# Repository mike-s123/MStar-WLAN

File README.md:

# MStar-WLAN

### What's new

Now supports collecting data in an [RRD](https://oss.oetiker.ch/rrdtool/), and charting that data using [JavascriptRRD](http://javascriptrrd.sourceforge.net). The interval for traditional logging can now be set. Updated hardware for USB Type-C.

## Overview

This project includes both a software and hardware design for interfacing to a [Morningstar](https://www.morningstarcorp.com/) solar controller via wireless LAN (WiFi). It's 99.99% working, with features still being added. The development core is an ESP32-WROVER-B 16MB (~$5 from Mouser) or an ESP32 DevkitC v4. A complete build should be ~$40, ignoring your time. Those platforms were chosen because they're available with a relatively large flash (16 MiB) for storing files, which allows having documentation and support for multiple solar controllers on-board. Supports MS-View compatible logging of controller info to an SD card, in addition to a debugging log. There's support for monitoring and configuration via a web interface, Modbus/TCP, and a RESTful JSON API. The UI fits well on a cell phone screen.

A core with less flash memory should work fine as long as the "data" directory will fit. The code supports moving content from flash to the SD Card. If a file is not found in flash, it will look for it on the SD Card. Delete everything in the "data" directory, copy everything from "data-small" into "data", and then copy everything in the "Put on SD Card - small" directory onto an SD Card to use an ESP32 board with less flash. The additional flash memory on the recommended modules is there in order to support all the static files even without an SD Card present. An SD Card is required for logging and charting.

It is written using the [Arduino IDE](https://www.arduino.cc/en/Main/Software), which is a bit "odd", hence code being split for clarity amongst multiple .h files. If you know how to do it better, please contribute. Yes, I know some of the code is butt-ugly. But it works. Function over form.

The printed circuit board was done in [Eagle](https://www.autodesk.com/products/eagle/overview).

Development has been done testing against the Prostar MPPT and Prostar PWM Gen3 controllers, and the information/config files for those have been provided. Other controllers will need to have register definition .csv files (see data/csv_file_desc.txt) added. Might need to do some work for register datatypes - Morningstar has many (really, what were they thinking creating one based on a 16 bit int, n·316.67·2^-15, and multiple similar) and they've changed over time. It should also be able to support Sunsavers (SSDuo, SS-MPPT), and Tristar (TS-45, TS-60, TS-MPPT-x) controllers (i.e. ones supporting Modbus). Morningstar isn't consistent with naming or numbering the registers, so such support will require more than just creating the .csv files. PS.h supports ProStar MPPT and PWM models and can be used as a template on how to support other models. Changes to _local.js_ may also be needed.

MODBUS-TCP works with Morningstar's MSView, allowing it to be used to monitor and configure a controller wirelessly. To do that, in MSView, do "Devices/Manual connection", select your controller type, select Connection Type Remote, and enter the IP address or DNS name of the MStar-WLAN. OK. Then right click on the controller in the left column and "connect." MSView first downloads any logs, so may take a minute before much else happens. It should work with any controller supporting MODBUS, it doesn't depend on the specific support for a controller, so if nothing else, it can be a wireless alternative to their USB/RS-232 to MeterBus converters (other than for doing firmware updates).

## Getting Started

The code will run on a bare ESP32 devboard, but obviously can't talk to a controller so the status and config pages won't do much. But you can check it out without much effort.

To do anything useful, hardware is needed to interface with a Morningstar controller. Morningstar uses a proprietary half-duplex (open collector, see /data/img/Schematic.png) Modbus interface. A circuit board layout is provided which includes all the necessary interfacing circuitry, even drawing power from the Morningstar controller. It supports an optional real time clock to support timestamped logging. It also supports ntp, so even without an RTC it can timestamp logs if it has a WLAN connection to the Internet.

Circuit board info is found in the "hardware/pcb" directory, where there are Eagle .brd, .sch and .lbr files, along with some parts info. The .zip file contains CAM files ready to send to [JLCPCB](https://jlcpcb.com/quote#/) to get boards made. Currently, 5 boards will cost you less than $10, if you will wait about a month to get them. The PCB was made to allow either "through hole" components (with an ESP32 DevkitC), or SMT ones (using a WROVER). If you use a DevkitC, note that 16 MiB ones aren't easy to find, so you'll probably still want to have the SD Card (which is needed for logging and charting).

I usually have a few circuit boards around. If you can contribute to the project, contact me and I might send you one. Even if you can't contribute, I might sell you one for a very reasonable price. If you don't solder, and want a pre-built one, contact me - this isn't meant to be a money maker (it's a hobby project), but I do value my time.

### Prerequisites

Development is currently being done with Arduino IDE 1.8.13, and tracking espressif / arduino-esp32ESP32 

Library requirements are noted in the .ino file. The [ESP32](https://github.com/espressif/arduino-esp32) core for Arduino needs to be installed. I follow the current development branch. View the README in the forArduinoIDE folder for info on setting up a custom board and partitions in the Arduino IDE (for Windoze, anyway).

Initially, the "data" directory needs to be uploaded to the board from the IDE (using the [arduino-esp32fs-plugin](https://github.com/me-no-dev/arduino-esp32fs-plugin)) or via OTA (Utility tab, will require files on the SD Card).

Uploadable code (MStar-WLAN.ino.esp32.bin) and flash (MStar-WLAN.littlefs.bin) binaries are provided here, which can be flashed using the OTA capability after the initial setup. 

The data/ctl/*.csv files are used to define the different controllers. data/csv_file_desc.txt describes the format.

## Operation

Using a standard "rollover" (tabs on the same side of the cable) 6P6C ("RJ12") cable, connect to the Meterbus port of a Morningstar controller. Don't worry - it's protected if wired wrong. A 4P4C cable should also work, if it's short (fewer wires for power).

The MStar-WLAN will initially come up as a wireless access point with SSID starting with "MStar" and a PSK of "morningstar". It will have an address of 192.168.4.1. 

The web interface has some minimal security. Any page which allows configuration changes is protected with default username "admin", password "setup". To do an Over-The-Air (OTA) firmware update or change security settings, the default username is "admin", password "update".

SSID, names and passwords can be changed (Utility tab, Security settings). To reset to defaults, press and hold the BOOT button for more than 5 seconds after powering up (WLAN LED will fast blink when you're held the button long enough).

Connecting to http://192.168.4.1/ will display the main status page. Other pages are shown along the top. "Utility/Wireless settings" will allow you to connect to a wireless network, from which the MStar-WLAN will get an address via DHCP (check your DHCP server to see what address it received). You can then connect to the internal web server at that address. The firmware also informs the DCHP server with a (statistically) unique hostname of the form "MStar-WLAN-xxxxxx", where the xs are the last 3 octets of the MAC address in hex.

OTA updates are done from the Utility tab, "Update WLAN module firmware" link. OTA updates of the flash (/data) image are also possible. File names are "MStar-WLAN.ino.esp32.bin" and "MStar-WLAN.littlefs.bin". 

## Known issues

When powered by the controller, it will sometimes reset at 2AM. I think this is somehow related to the ezTime library, which is really the only thing that time is special to (it's the DST changeover time for my timezone). It doesn't seem to happen when powered by USB, and doesn't seem to happen with a PS-MPPT (only a PWM). Perhaps a short race condition which causes a greater than normal power draw. It's not a big issue - the solar controller isn't affected, and we'll simply reboot and resume operation in about a minute.

## Support

There is none, although you can certainly ask - if you're having a problem, you've probably found something which I'll eventually run into. You'll get a better response if you can well document a bug. This was a personal project, I'm freely offering it to others for non-commercial use. Feel free to contribute back if you can (don't do github pull requests, that would just be another thing for me to figure out how to make work, I'm not a regular git user.). Things which need attention or might be an important future direction are commented with "TODO".

## General answers to any question (pick one)

Yes.

No.

That's an important future direction.

That's a significant third-party opportunity.

## More Info

More info may be found under the data directory.

## Current work

The hardware supports one of the cheap Chinese DS3231 Real Time Clock boards. The software can be configured to connect to an NTP server, and if it does it will keep the RTC in sync (and trim its oscillator more accurately, too!). Either a good network connection is needed (for NTP), or an RTC, for accurate logging. 

## Important future directions

Possible additions: Include support for additional controllers (if someone has a broken one which might still talk MODBUS, feel free to donate). <s>Allow changing user/pass for config and update.</s> Static IP config. SMTP - email notifications for error or out-of-range conditions (or even daily updates). <s>Logging/graphing.</s> Support for simultaneous connection to multiple controllers. <s>Async web server.</s> Chunked responses. Provide "one click" charging settings for different batteries. Backup/restore settings. <s>Support connection to multiple, alternate SSIDs</s> (done). MQTT. SNMP. Serial passthrough, to allow a direct MS-View connection and firmware upgrades via USB. <s>Move large files to SD card.</s> ???.
 
## Author

* **Mike Sauve** - [mike-s123](https://github.com/mike-s123/)
Programming is not my day job, so don't be harsh about style or efficiency. Function over form. It's working for me, I hope it works for you. I formally learned on FORTRAN and PL/C. Later BASIC, assembly, and bash with a small bit of python. 98% as a hobby. OO stuff is foreign to me. 

## License and copyrights

First up - if you clone/fork this, please let me know. It's not a requirement, just a request - I'd like to know who else is interested - I haven't found much interest/development for similar projects.

* Original work copyright by Mike Sauve, License [CC BY-NC](https://creativecommons.org/licenses/by-nc/4.0/legalcode)

* See [LICENSE.MD](https://github.com/mike-s123/MStar-WLAN/blob/master/LICENSE.md) for more detail.

* Hardware datasheets (in the hardware directory) are copyrighted by the manufacturers. They were all pulled off public websites. I believe it is fair use to have them here, where they're doing what they were intended to do - support the associated devices. If any complain, I'll remove them.

* Morningstar documentation (in data directory) is copyrighted by Morningstar. All of it was pulled off their public website, it is here simply to make things easier. I believe it is fair use to have them here, same reason as above. If Morningstar complains, I'll remove them.

* All libraries are copyright their respective owners. I think I've provided proper credit to all, and suitable links to the licenses.

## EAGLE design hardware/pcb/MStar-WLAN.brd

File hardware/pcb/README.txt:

Notes:
The .zip file in this folder is ready to submit to https://jlcpcb.com/ where you can get 5 boards, shipped for about US$10.

Components can be ordered through Mouser using this convenient cart: https://www.mouser.com/ProjectManager/ProjectDetail.aspx?AccessID=f1275ffe09

The other files are schematic, board layout, library and CAM processor files for Eagle CAD.

MStar-WLAN parts notes

Notes: C1 should be large, C12 low ESR. The power provided by the controller isn't always steady. The VR needs to be a switcher, a linear consumes too much power. The voltage regulator below seems to work best of those I tried, it's quite efficient in this application. As shown on the schematic, many parts are only needed if using a WROVER.

Resistors and caps aren't critical, other than below. Note that the resistor footprints are for miniature (3.4mm) ones.

Most parts are standard, these are somewhat specific:
C1 - Panasonic EEU-FR1V222L (2200 uF/35 VDC)
C12 - should be low ESR (Panasonic 	EEU-FS0J202LB 2000 uF/6.3 VDC)
D2 - Vishay SB140-E3, due to its low Vf.
VR1 - OKI-78SR-3.3/1.5-W36-C, supports large capacitive loads
VR2 - STM LDL1117S33R SOT-223-4 (only with WROVER)
J1 - 6P6C connector - Kycon GLX-N-66
J2 - SD Card - Hirose DM3BT-DSF-PEJS Note the contacts are away from the board.
J3 - USB C - JAE DX07S016JA3 This is the most difficult to hand solder SMD on the board. (only with WROVER)
Case - Hammond RL6105, board mounts to cover
USB/Serial - FTDI FT231XS-R SSOP-20 (only with WROVER) - to be correct, use ftprog (https://www.ftdichip.com/Support/Utilities.htm#FT_PROG) to program the chip with the FT231X.xml template, which tells the host to provide 500 mA to power the board when connected to a USB 2.1 host.
Reset - Rohm IMH3AT110 SOT-457 (only with WROVER)
TVS - BZW04-33 33V unidirectional

RTC - Not included in the Mouser project BOM. DS3231(common ZS-042 module, search Amazon for DS3231) Note that the header is installed on the side opposite the battery, so the battery is accessible when the module is in place. The module also needs to be modified so it doesn't try to charge the battery (remove the LED while you're at it). https://www.onetransistor.eu/2019/07/zs042-ds3231-battery-charging-circuit.html

- potential future for on-board RRD logging - FRAM Cypress CY15B108QN-40SXI (expensive, but 10^15 cycles) Fujitsu ‎MB85AS8MTPF-G-KBERE1‎ (not FRAM, ReRAM, but 1000000 cycles) Unfortunately, sharing SPI with the SD Card currently has issues.

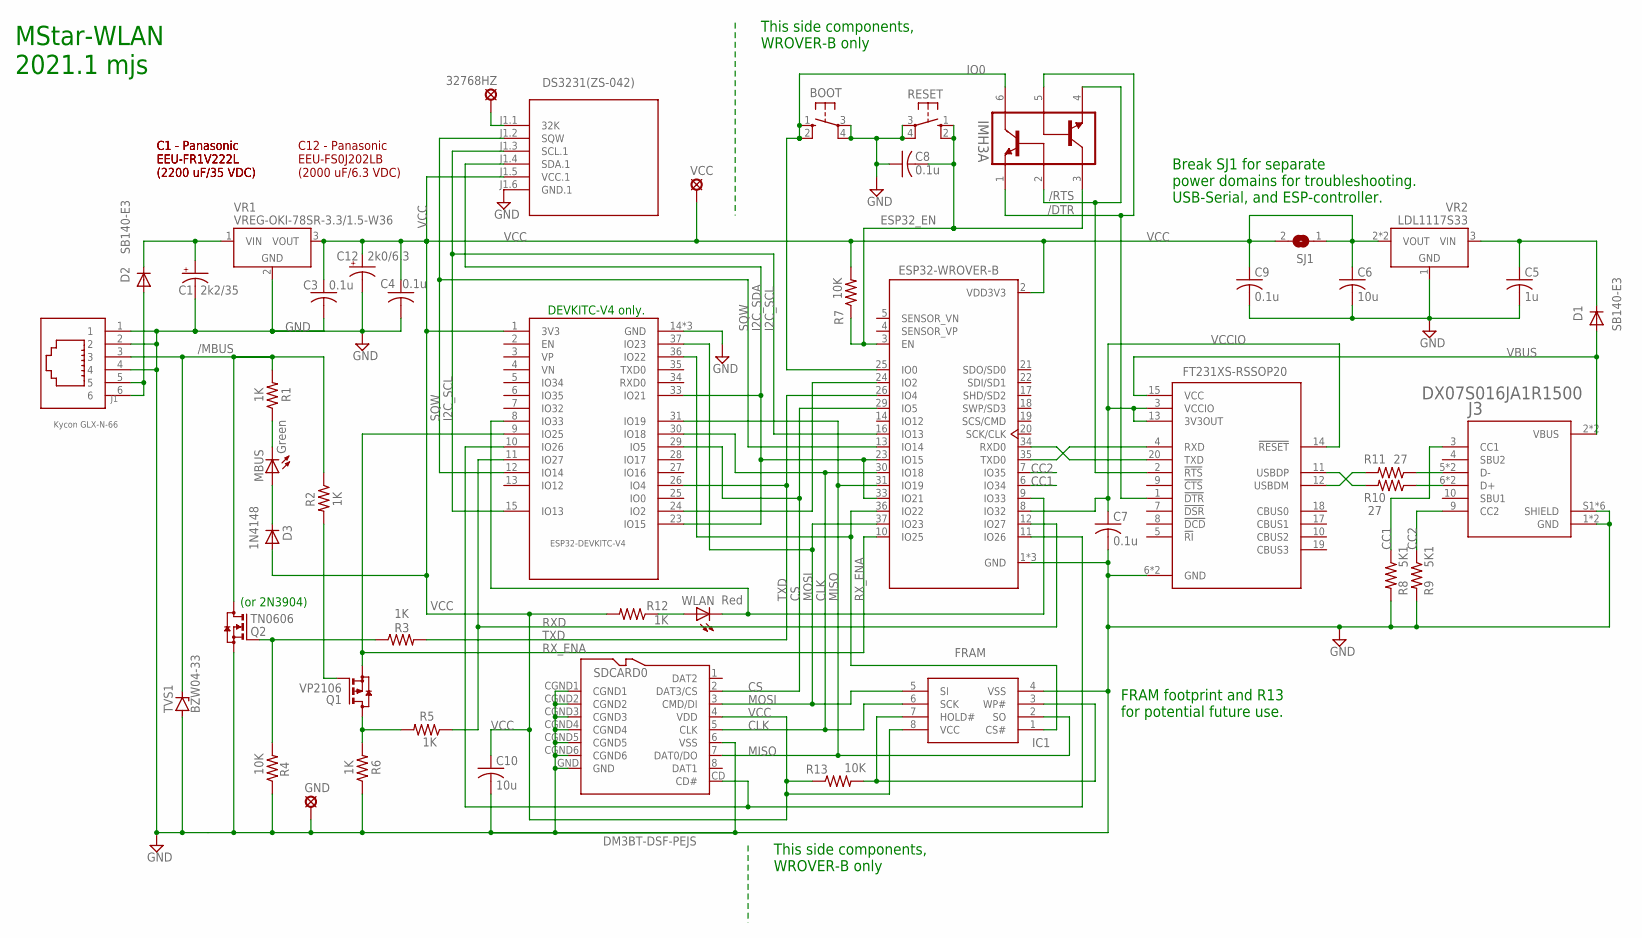
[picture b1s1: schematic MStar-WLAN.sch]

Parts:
32768HZ: MCS10B
BOOT: PTS645SM432LFS; B3F-10XX
C1: 2k2/35; E5-4
C3, C4, C7, C8, C9: 0.1u; C025-024X044
C5: 1u; C1206
C6, C10: 10u; C1206
C12: 2k0/6.3; E5-6
D1, D2: SB140-E3; DO41-7.6
D3: 1N4148; DO35-7
DS3231(ZS-042): RTC-DS3231-AT24C32-6
ESP32-WROVER-B: ESP32-WROVER-I; XCVR_ESP32-WROVER-I
FT231XS: FT231XS-RSSOP20; SSOP20
GND: MCS10B
IC1: FRAM; SO-08M
IMH3A: IMH3ATSOP6; TSOP6
J1: Kycon GLX-N-66; 6P6C
J3: DX07S016JA1R1500; JAE_DX07S016JA1R1500
MBUS: Green; LED3MM
Q1: VP2106; TO92
Q2: TN0606; TO92
R1, R2, R3, R5, R6, R12: 1K; 0204/5
R4, R7: 10K; 0204/5
R8, R9: 5K1; 0204/5
R10, R11: 27; 0204/5
R13: 10K; R1206
RESET: PTS645SM432LFS; B3F-10XX
SDCARD0: DM3BT-DSF-PEJS
SJ1: SJ
TVS1: BZW04-33; DO41Z10
U$1: ESP32-DEVKITC-V4-NOSD
VCC: MCS10B
VR1: VREG-OKI-78SR-3.3/1.5-W36; OKI-78SR
VR2: LDL1117S33; SOT223
WLAN: Red; LED3MM

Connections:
/DTR: FT231XS.1 (!DTR), IMH3A.1 (Q1E), IMH3A.5 (Q2B)
/MBUS: J1.3, Q2.D, R1.2, R2.1, TVS1.C
/RTS: FT231XS.2 (!RTS), IMH3A.2 (Q1B), IMH3A.4 (Q2E)
CC1: ESP32-WROVER-B.6 (IO34), J3.3 (CC1), R8.1
CC2: ESP32-WROVER-B.7 (IO35), J3.9 (CC2), R9.1
CD: ESP32-WROVER-B.11 (IO26), SDCARD0.CD (CD#), U$1.10 (IO26)
CLK: ESP32-WROVER-B.30 (IO18), IC1.6 (SCK), SDCARD0.5 (CLK), U$1.30 (IO18)
CS: ESP32-WROVER-B.29 (IO5), SDCARD0.2 (DAT3/CS), U$1.29 (IO5)
ESP32_EN: C8.2, ESP32-WROVER-B.3 (EN), IMH3A.3 (Q2C), R7.1, RESET.1 (S), RESET.2 (S1)
GND: BOOT.3, BOOT.4 (P1), C1.-, C3.2, C4.2, C5.2, C6.2, C7.2, C8.1, C9.2, C10.2, C12.-, DS3231(ZS-042).J1.6 (GND.1), ESP32-WROVER-B.1 (GND), ESP32-WROVER-B.15 (GND), ESP32-WROVER-B.38 (GND), FT231XS.6 (GND), FT231XS.16 (GND), GND.MP, IC1.4 (VSS), J1.1, J1.2, J1.4, J3.1 (GND), J3.12 (GND), J3.S1 (SHIELD), J3.S2 (SHIELD), J3.S3 (SHIELD), J3.S4 (SHIELD), J3.S5 (SHIELD), J3.S6 (SHIELD), Q2.S, R4.1, R6.1, R8.2, R9.2, RESET.3, RESET.4 (P1), SDCARD0.6 (VSS), SDCARD0.CGND1, SDCARD0.CGND2, SDCARD0.CGND3, SDCARD0.CGND4, SDCARD0.CGND5, SDCARD0.CGND6, SDCARD0.GND, TVS1.A, U$1.14 (GND), U$1.32 (GND), U$1.38 (GND), VR1.2 (GND), VR2.1 (GND)
I2C_SCL: DS3231(ZS-042).J1.3 (SCL.1), ESP32-WROVER-B.16 (IO13), U$1.15 (IO13)
I2C_SDA: DS3231(ZS-042).J1.4 (SDA.1), ESP32-WROVER-B.23 (IO15), ESP32-WROVER-B.33 (IO21), U$1.23 (IO15), U$1.33 (IO21)
IO0: BOOT.1 (S), BOOT.2 (S1), ESP32-WROVER-B.25 (IO0), IMH3A.6 (Q1C)
MISO: ESP32-WROVER-B.31 (IO19), IC1.2 (SO), SDCARD0.7 (DAT0/DO), U$1.31 (IO19)
MOSI: ESP32-WROVER-B.37 (IO23), IC1.5 (SI), SDCARD0.3 (CMD/DI), U$1.37 (IO23)
unnamed: MBUS.K (C), R1.1
unnamed: Q2.G, R3.1, R4.2
unnamed: Q1.G, R2.2
unnamed: 32768HZ.MP, DS3231(ZS-042).J1.1 (32K)
unnamed: ESP32-WROVER-B.36 (IO22), IC1.1 (CS#), U$1.36 (IO22)
unnamed: IC1.3 (WP#), IC1.7 (HOLD#), R13.2
unnamed: D3.C, MBUS.A
unnamed: ESP32-WROVER-B.24 (IO2), U$1.24 (IO2)
unnamed: Q1.D, R5.2, R6.2
unnamed: D2.A, J1.5, J1.6
unnamed: C5.1, D1.C, VR2.3 (VIN)
unnamed: R12.1, WLAN.A
RAW12: C1.+, D2.C, VR1.1 (VIN)
RXD: ESP32-WROVER-B.12 (IO27), R5.1, U$1.11 (IO27)
RXD0: ESP32-WROVER-B.34 (RXD0), FT231XS.20 (TXD)
RX_ENA: ESP32-WROVER-B.10 (IO25), Q1.S, U$1.9 (IO25)
SQW: DS3231(ZS-042).J1.2 (SQW), ESP32-WROVER-B.13 (IO14), U$1.12 (IO14)
TXD: ESP32-WROVER-B.26 (IO4), R3.2, U$1.26 (IO4)
TXD0: ESP32-WROVER-B.35 (TXD0), FT231XS.4 (RXD)
USBD+: J3.6 (D+), J3.7 (D+), R10.1
USBD-: J3.5 (D-), J3.8 (D-), R11.1
USBDM: FT231XS.12 (USBDM), R11.2
USBDP: FT231XS.11 (USBDP), R10.2
VBUS: D1.A, FT231XS.15 (VCC), J3.2 (VBUS), J3.11 (VBUS)
VCC: C3.1, C4.1, C6.1, C9.1, C10.1, C12.+, D3.A, DS3231(ZS-042).J1.5 (VCC.1), ESP32-WROVER-B.2 (VDD3V3), IC1.8 (VCC), R7.2, R12.2, R13.1, SDCARD0.4 (VDD), SJ1.1, SJ1.2, U$1.1 (3V3), VCC.MP, VR1.3 (VOUT), VR2.2 (VOUT), VR2.4 (VOUT)
VCCIO: C7.1, ESP32-WROVER-B.8 (IO32), FT231XS.3 (VCCIO), FT231XS.13 (3V3OUT), FT231XS.14 (!RESET)
WLAN_LED: ESP32-WROVER-B.9 (IO33), U$1.8 (IO33), WLAN.K (C)

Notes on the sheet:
MStar-WLAN 2021.1 mjs
C1 - Panasonic EEU-FR1V222L (2200 uF/35 VDC)
This side components, WROVER-B only
DEVKITC-V4 only.
(or 2N3904)
C12 - Panasonic EEU-FS0J202LB (2000 uF/6.3 VDC)
Break SJ1 for separate power domains for troubleshooting. USB-Serial, and ESP-controller.
FRAM footprint and R13 for potential future use.

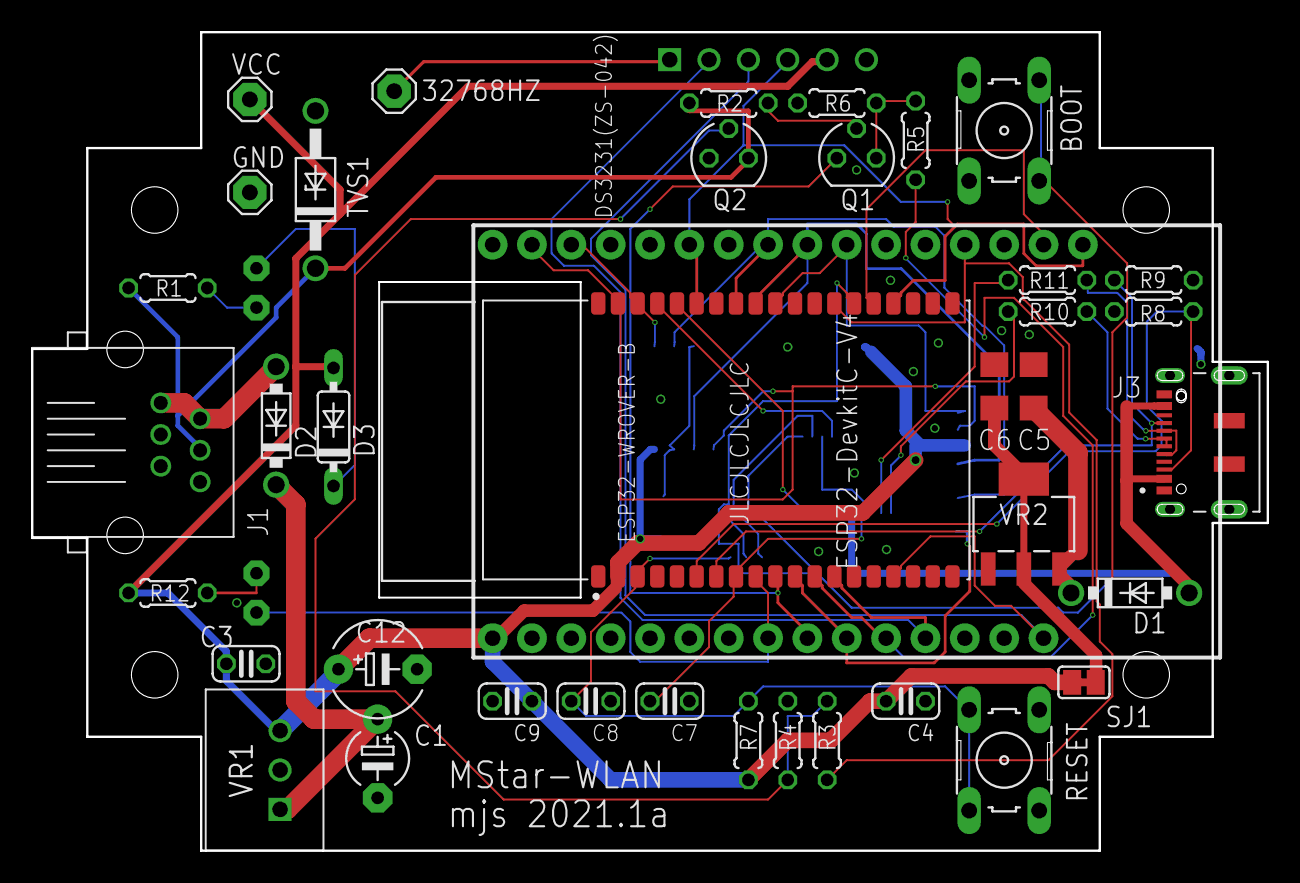
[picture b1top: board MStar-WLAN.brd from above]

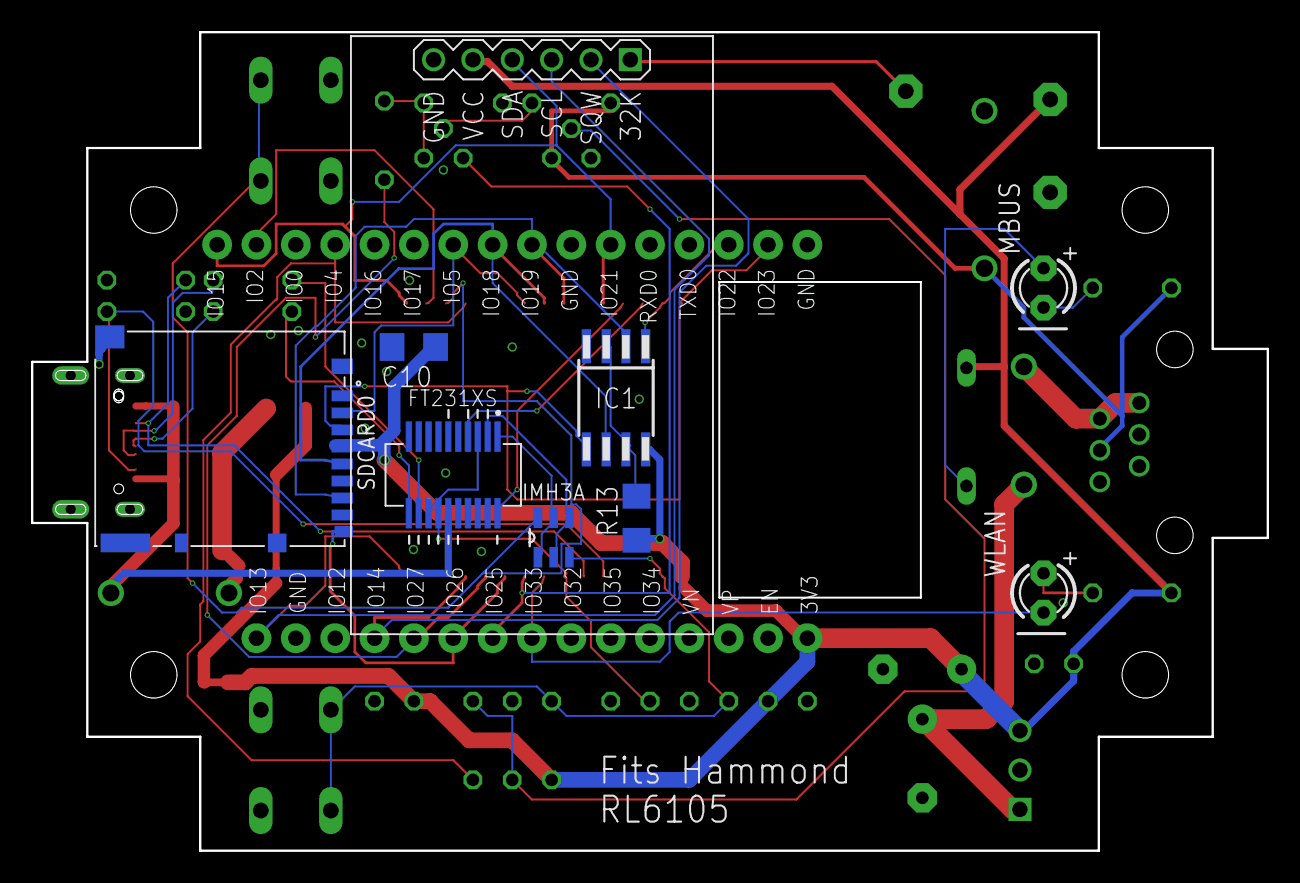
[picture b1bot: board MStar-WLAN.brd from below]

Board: 2 copper layers, 79.8 x 52.8 mm, 48 parts (9 on the bottom side), 42 nets.

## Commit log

2019-11-24 more files
2019-11-24 clean up
2019-11-24 pictures
2019-11-24 fixed RTC check
2019-11-24 linguist
2019-11-25 doc update
2019-12-03 work on LittleFS
2019-12-03 dynamic hostname
2019-12-04 LittleFS, README
2019-12-04 spiffs
2019-12-04 littlefs support
2019-12-09 littlefs, editor
2019-12-09 editor
2019-12-09 README
2019-12-09 licenses
2019-12-11 add more datatypes
2019-12-12 speed up, auto-refresh
2019-12-12 better auto-refresh
2019-12-12 re-do debug port
2019-12-13 mDNS
2019-12-15 reorg flash
2019-12-16 refactor
2019-12-18 ESP32 work
2019-12-18 wifiMulti
2019-12-19 WLAN robustness. WIFI_AP_STA support
2019-12-19 add comments
2019-12-21 more WLAN work
2019-12-22 ntp support
2019-12-23 more time
2019-12-23 cosmetics, minor fixes
2019-12-24 clean up, ntp fix
2019-12-27 refactor, auto RTC adjust
2019-12-31 time fixes, REST improvements
2020-01-03 more time fixes, prep for SD Card
2020-01-06 bug fixes. SD Card support. New PCB.
2020-01-08 redo debug logging, bug fixes
2020-02-09 fixes, controller logging
2020-02-09 logging fix
2020-02-12 hardware update
2020-05-26 ESP32. Logging. Dynamic status update. More.
2020-05-26 Fix markdown
2020-07-04 tweak RTC adjustment
2020-10-07 improve discovery
2020-10-07 ignore js, css
2020-10-22 Allow WLAN and security settings.
2020-10-22 Update README.
2020-10-22 Update Data and spiffs file
2020-10-22 Clean up 8266 cruft.
2020-10-23 Put AP config in the same place.
2020-10-23 Modbus error stats.
2020-10-23 Improve OTA logging
2020-10-23 Update version
2020-10-25 Mbus work.
2020-10-30 Logging, hardware change to USB C
2020-10-31 Fix setTime buttons
2020-11-01 Add reset to default (press BOOT for 5+ s)
2020-11-06 hardware, configurable hostname
2020-11-07 REST fixes
2020-11-08 Rearrange platform page
2020-11-08 Arduino IDE work
2020-11-08 Cosmetic
2020-11-08 Arduino IDE
2020-11-09 new compile
2020-11-11 OTA improvment
2020-11-11 Mbus improvement
2020-11-11 fixes/cleanups
2020-11-13 logging, small flash support
2020-11-13 fix sd card size
2020-11-18 fancy LED
2020-11-21 LED done by hardware, logging spares
2020-11-21 change log to .csv
2020-11-21 minor logging fix
2020-11-23 change to LITTLEFS
2020-11-24 littlefs cleanup
2020-11-25 minor
2020-11-25 OTA improvements
2020-11-25 serve OTA.js from PROGMEM
2020-11-26 server local.* from PROGMEM
2020-11-26 consolidate MIME types
2020-11-26 MIME types
2020-11-26 prefer files from SD Card, configurable debug
2020-11-27 logging changes
2020-11-28 logging, REST timeout
2020-12-11 REST, Modbus, logging, Preferences
2020-12-12 minor fixes
2021-01-14 Hardware, charting, much more
    Hardware updated for USB-C and to support Devkit-C.
    Charting using an RRD database and JavascriptRRD / FLOT.
    Show temperature in C or F on /status page.
    Configurable logging period for traditional log.
    Lots of bug fixes and tweaks, especially in Modbus.
2021-01-14 update hardware info
2021-01-16 Redo MaxP, chart tweaks
2021-01-20 fix solar power calc
2021-02-01 maxP logging, minor fixes/tweaks
